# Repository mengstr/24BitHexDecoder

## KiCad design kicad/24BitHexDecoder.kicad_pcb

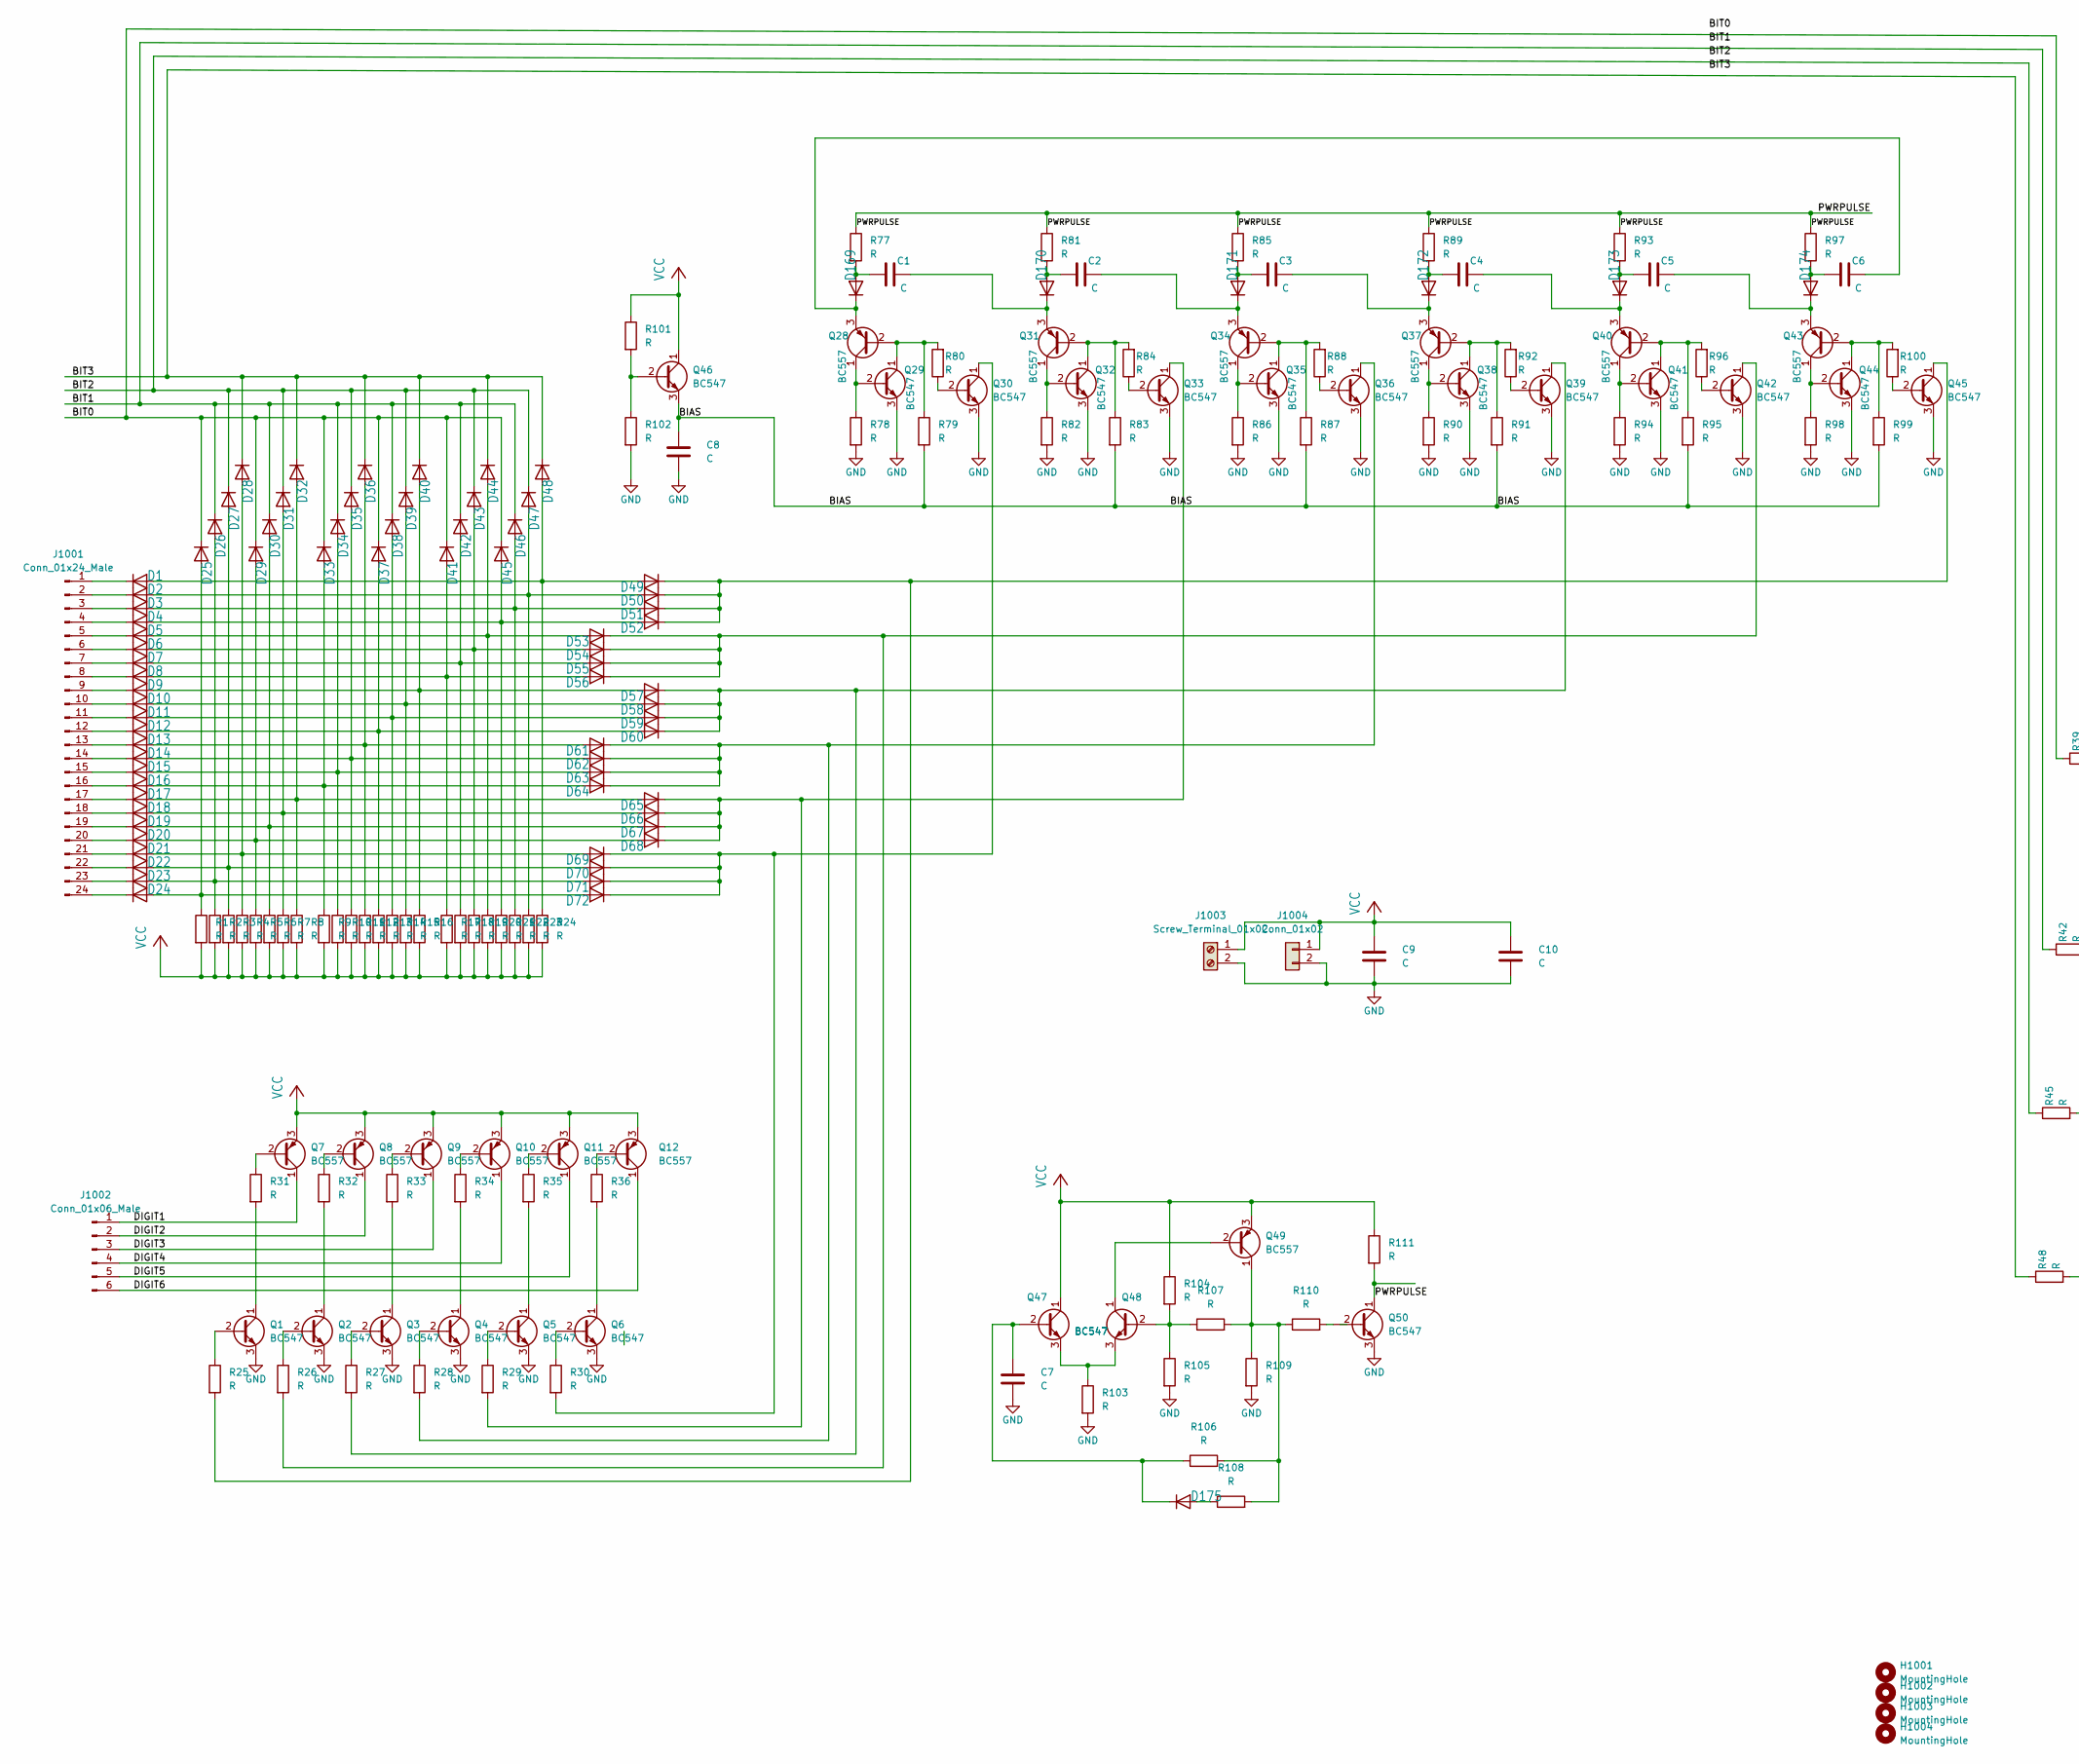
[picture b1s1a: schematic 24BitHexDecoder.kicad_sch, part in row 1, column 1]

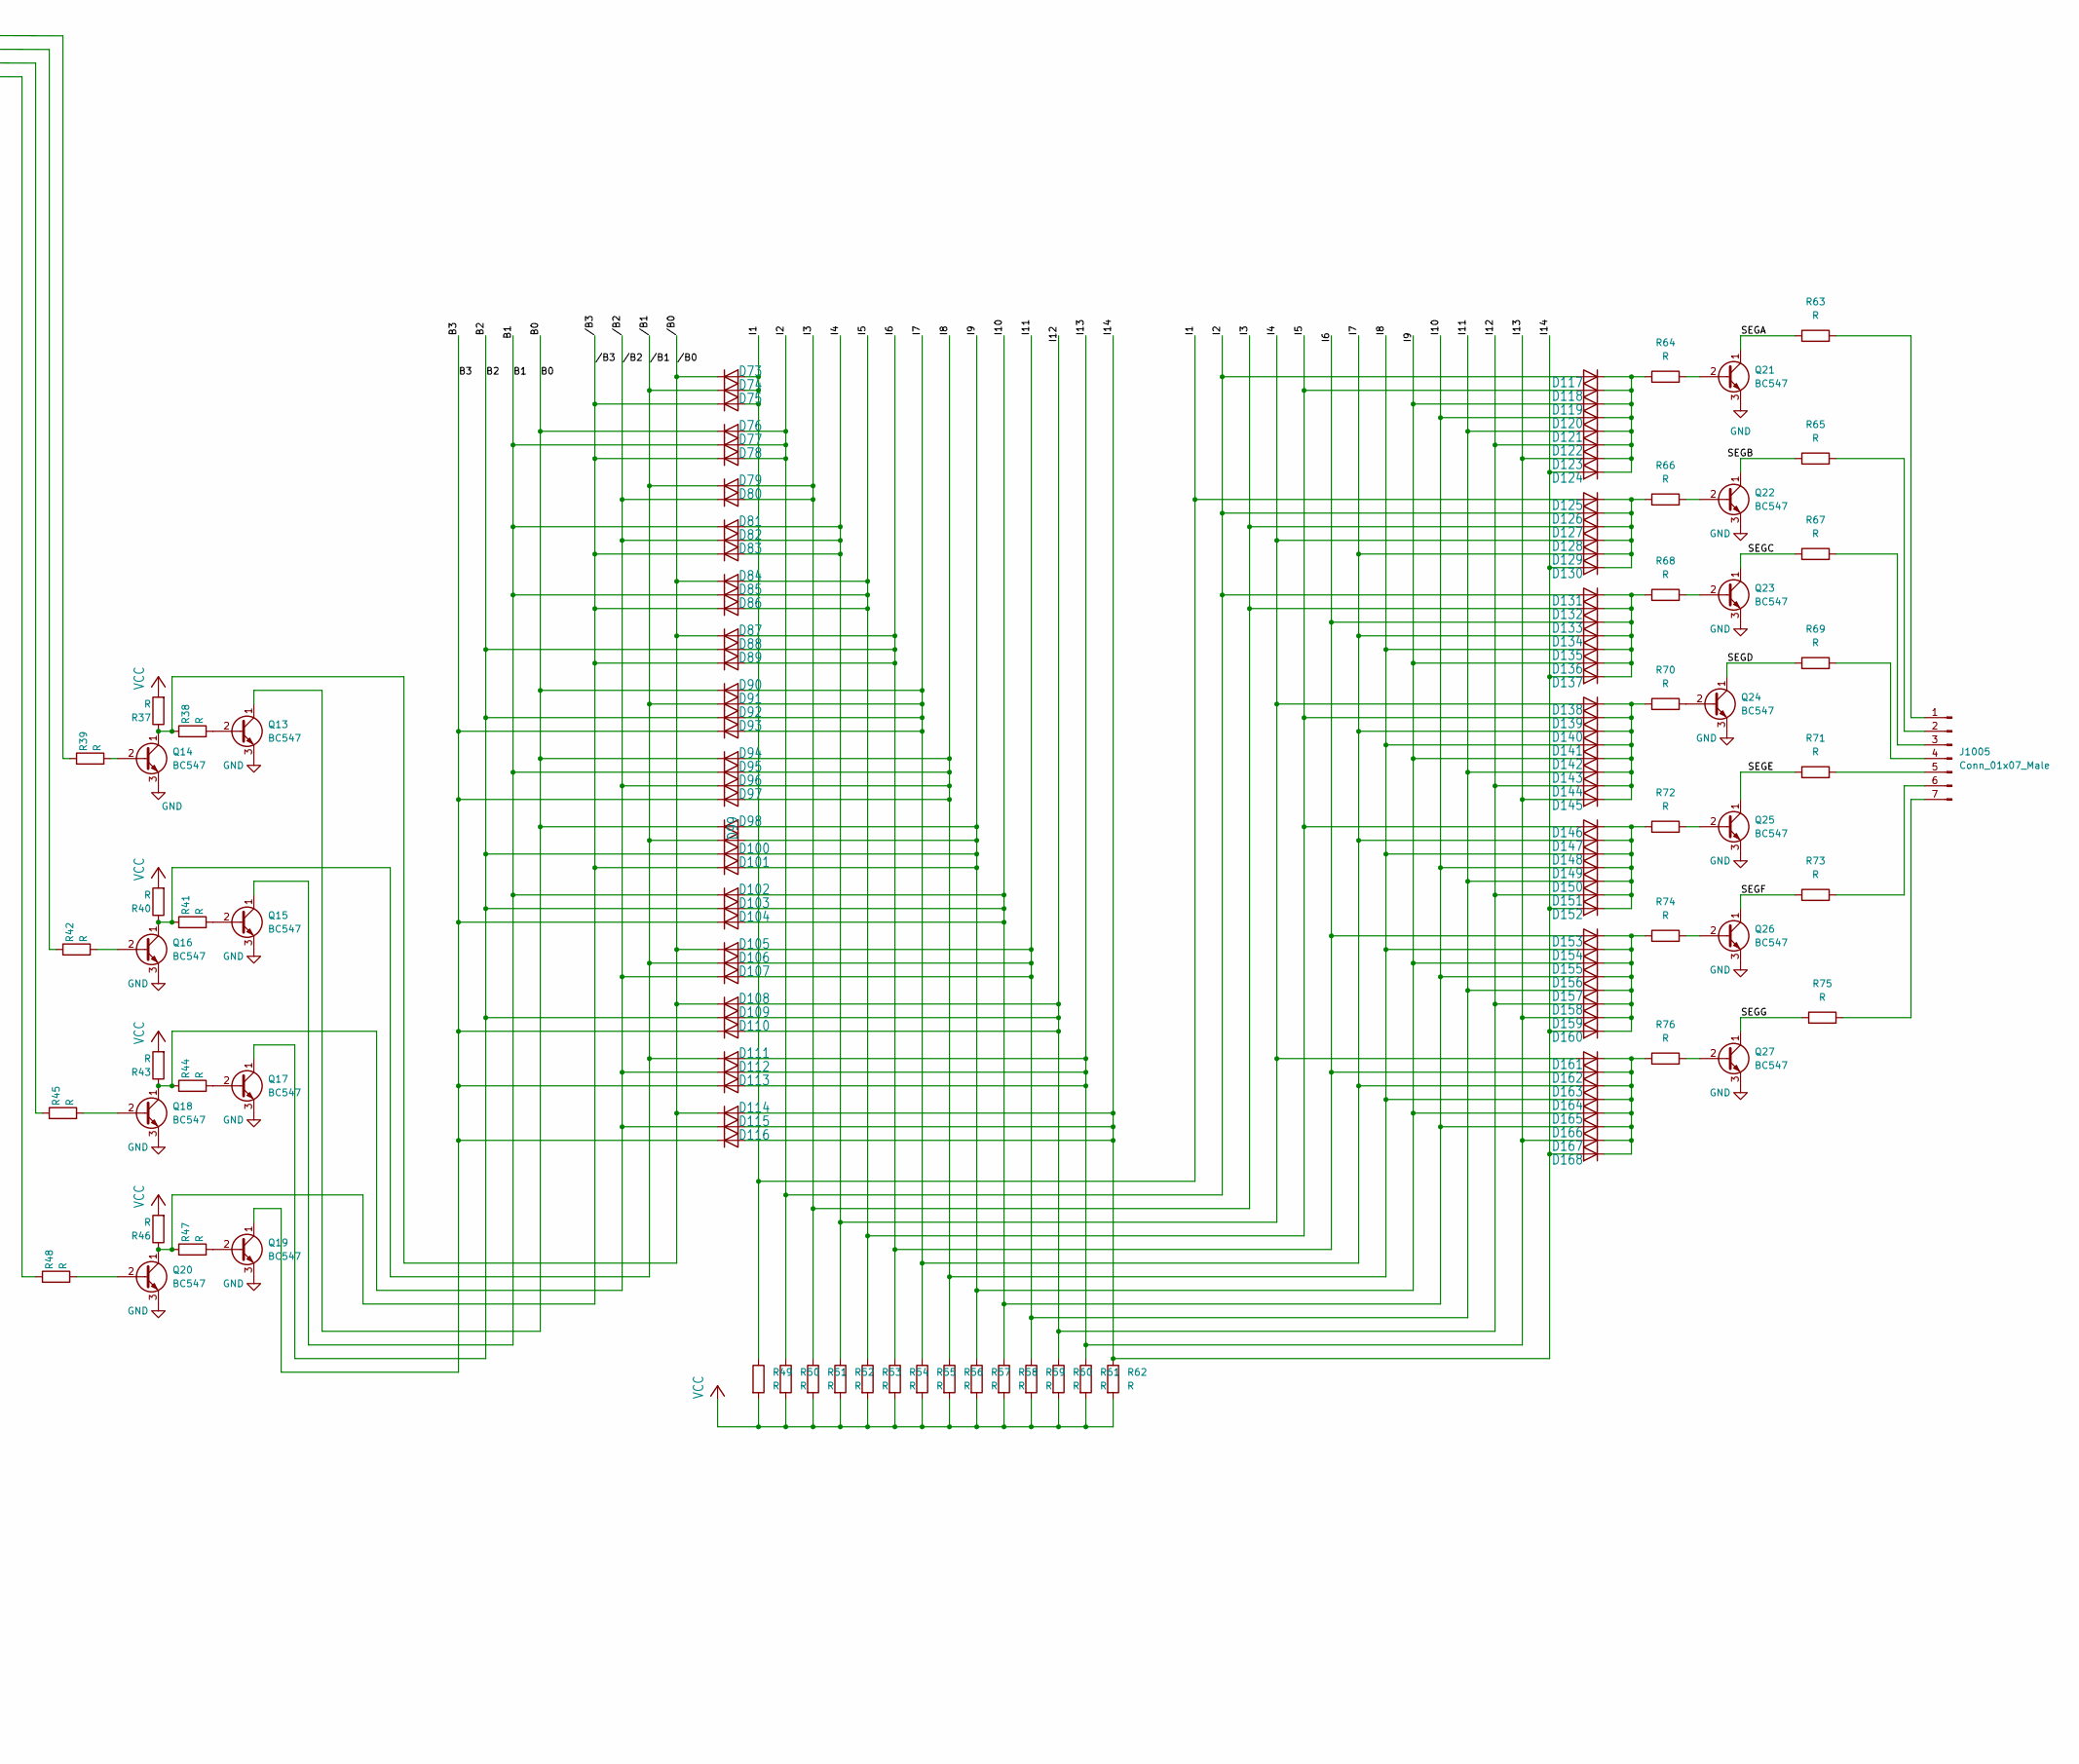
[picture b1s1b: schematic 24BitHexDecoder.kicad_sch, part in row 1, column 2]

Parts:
C1, C2, C3, C4, C5, C6, C7: C; C_Disc_D9.0mm_W2.5mm_P5.00mm
C8, C9, C10: C; CP_Radial_D5.0mm_P2.50mm
D1, D2, D3, D4, D5, D6, D7, D8, D9, D10, D11, D12, D13, D14, D15, D16, D17, D18, D19, D20, D21, D22, D23, D24, D25, D26, D27, D28, D29, D30, D31, D32, D33, D34, D35, D36, D37, D38, D39, D40, D41, D42, D43, D44, D45, D46, D47, D48, D49, D50, D51, D52, D53, D54, D55, D56, D57, D58, D59, D60, D61, D62, D63, D64, D65, D66, D67, D68, D69, D70, D71, D72, D73, D74, D75, D76, D77, D78, D79, D80, D81, D82, D83, D84, D85, D86, D87, D88, D89, D90, D91, D92, D93, D94, D95, D96, D97, D98, D99, D100, D101, D102, D103, D104, D105, D106, D107, D108, D109, D110, D111, D112, D113, D114, D115, D116, D117, D118, D119, D120, D121, D122, D123, D124, D125, D126, D127, D128, D129, D130, D131, D132, D133, D134, D135, D136, D137, D138, D139, D140, D141, D142, D143, D144, D145, D146, D147, D148, D149, D150, D151, D152, D153, D154, D155, D156, D157, D158, D159, D160, D161, D162, D163, D164, D165, D166, D167, D168, D169, D170, D171, D172, D173, D174, D175: SMALL_DIODEDO35-7; D_DO-35_P7.62_SmallPads
H1001, H1002, H1003, H1004: MountingHole; MountingHole_3.2mm_M3
J1001: Conn_01x24_Male; PinHeader_1x24_P2.54mm_Vertical
J1002: Conn_01x06_Male; PinHeader_1x06_P2.54mm_Vertical
J1003: Screw_Terminal_01x02; TerminalBlock_TE_282834-2_1x02_P2.54mm_Horizontal
J1004: Conn_01x02; PinHeader_1x02_P2.54mm_Vertical
J1005: Conn_01x07_Male; PinHeader_1x07_P2.54mm_Vertical
Q1, Q2, Q3, Q4, Q5, Q6, Q13, Q14, Q15, Q16, Q17, Q18, Q19, Q20, Q21, Q22, Q23, Q24, Q25, Q26, Q27, Q29, Q30, Q32, Q33, Q35, Q36, Q38, Q39, Q41, Q42, Q44, Q45, Q46, Q47, Q48, Q50: BC547; TO-92_NPN_Spaced
Q7, Q8, Q9, Q10, Q11, Q12, Q28, Q31, Q34, Q37, Q40, Q43, Q49: BC557; TO-92_PNP_Spaced
R1, R2, R3, R4, R5, R6, R7, R8, R9, R10, R11, R12, R13, R14, R15, R16, R17, R18, R19, R20, R21, R22, R23, R24, R25, R26, R27, R28, R29, R30, R31, R32, R33, R34, R35, R36, R37, R38, R39, R40, R41, R42, R43, R44, R45, R46, R47, R48, R49, R50, R51, R52, R53, R54, R55, R56, R57, R58, R59, R60, R61, R62, R63, R64, R65, R66, R67, R68, R69, R70, R71, R72, R73, R74, R75, R76, R77, R78, R79, R80, R81, R82, R83, R84, R85, R86, R87, R88, R89, R90, R91, R92, R93, R94, R95, R96, R97, R98, R99, R100, R101, R102, R103, R104, R105, R106, R107, R108, R109, R110, R111: R; R_L3.6mm_D1.6mm_P7.62mm_NoTop

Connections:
/B0: D76.1 (K), D90.1 (K), D94.1 (K), D98.1 (K), Q13.1 (C)
/B1: D77.1 (K), D81.1 (K), D85.1 (K), D95.1 (K), D102.1 (K), Q15.1 (C)
/B2: D88.1 (K), D92.1 (K), D100.1 (K), D103.1 (K), D109.1 (K), Q17.1 (C)
/B3: D93.1 (K), D97.1 (K), D104.1 (K), D110.1 (K), D113.1 (K), D116.1 (K), Q19.1 (C)
/BIAS: C8.1, Q46.3 (E), R79.2, R83.2, R87.2, R91.2, R95.2, R99.2
/BIT0: D25.1 (K), D29.1 (K), D33.1 (K), D37.1 (K), D41.1 (K), D45.1 (K), R39.1
/BIT1: D26.1 (K), D30.1 (K), D34.1 (K), D38.1 (K), D42.1 (K), D46.1 (K), R42.1
/BIT2: D27.1 (K), D31.1 (K), D35.1 (K), D39.1 (K), D43.1 (K), D47.1 (K), R45.1
/BIT3: D28.1 (K), D32.1 (K), D36.1 (K), D40.1 (K), D44.1 (K), D48.1 (K), R48.1
/DIGIT1: J1002.1, Q7.1 (C)
/DIGIT2: J1002.2, Q8.1 (C)
/DIGIT3: J1002.3, Q9.1 (C)
/DIGIT4: J1002.4, Q10.1 (C)
/DIGIT5: J1002.5, Q11.1 (C)
/DIGIT6: J1002.6, Q12.1 (C)
/I1: D73.2 (A), D74.2 (A), D75.2 (A), D125.2 (A), R49.1
/I2: D76.2 (A), D77.2 (A), D78.2 (A), D117.2 (A), D126.2 (A), D131.2 (A), R50.1
/I3: D79.2 (A), D80.2 (A), D127.2 (A), D132.2 (A), R51.1
/I4: D81.2 (A), D82.2 (A), D83.2 (A), D128.2 (A), D138.2 (A), D161.2 (A), R52.1
/I5: D84.2 (A), D85.2 (A), D86.2 (A), D118.2 (A), D139.2 (A), D146.2 (A), R53.1
/I6: D87.2 (A), D88.2 (A), D89.2 (A), D133.2 (A), D153.2 (A), D162.2 (A), R54.1
/I7: D90.2 (A), D91.2 (A), D92.2 (A), D93.2 (A), D129.2 (A), D134.2 (A), D140.2 (A), D147.2 (A), D163.2 (A), R55.1
/I8: D94.2 (A), D95.2 (A), D96.2 (A), D97.2 (A), D135.2 (A), D141.2 (A), D148.2 (A), D154.2 (A), D164.2 (A), R56.1
/I9: D98.2 (A), D99.2 (A), D100.2 (A), D101.2 (A), D119.2 (A), D136.2 (A), D142.2 (A), D155.2 (A), D165.2 (A), R57.1
/I10: D102.2 (A), D103.2 (A), D104.2 (A), D120.2 (A), D149.2 (A), D156.2 (A), D166.2 (A), R58.1
/I11: D105.2 (A), D106.2 (A), D107.2 (A), D121.2 (A), D143.2 (A), D150.2 (A), D157.2 (A), R59.1
/I12: D108.2 (A), D109.2 (A), D110.2 (A), D122.2 (A), D144.2 (A), D151.2 (A), D158.2 (A), R60.1
/I13: D111.2 (A), D112.2 (A), D113.2 (A), D123.2 (A), D145.2 (A), D159.2 (A), D167.2 (A), R61.1
/I14: D114.2 (A), D115.2 (A), D116.2 (A), D124.2 (A), D130.2 (A), D137.2 (A), D152.2 (A), D160.2 (A), D168.2 (A), R62.1
/PWRPULSE: Q50.1 (C), R77.1, R81.1, R85.1, R89.1, R93.1, R97.1, R111.2
/SEGA: Q21.1 (C), R63.1
/SEGC: Q23.1 (C), R67.1
/SEGD: Q24.1 (C), R69.1
/SEGE: Q25.1 (C), R71.1
/SEGF: Q26.1 (C), R73.1
/SEGG: Q27.1 (C), R75.1
//B0: D73.1 (K), D84.1 (K), D87.1 (K), D105.1 (K), D108.1 (K), D114.1 (K), Q14.1 (C), R37.1, R38.1
//B1: D74.1 (K), D79.1 (K), D91.1 (K), D99.1 (K), D106.1 (K), D111.1 (K), Q16.1 (C), R40.1, R41.1
//B2: D80.1 (K), D82.1 (K), D96.1 (K), D107.1 (K), D112.1 (K), D115.1 (K), Q18.1 (C), R43.1, R44.1
//B3: D75.1 (K), D78.1 (K), D83.1 (K), D86.1 (K), D89.1 (K), D101.1 (K), Q20.1 (C), R46.1, R47.1
GND: C7.2, C8.2, C9.2, C10.2, J1003.2, J1004.2, Q1.3 (E), Q2.3 (E), Q3.3 (E), Q4.3 (E), Q5.3 (E), Q6.3 (E), Q13.3 (E), Q14.3 (E), Q15.3 (E), Q16.3 (E), Q17.3 (E), Q18.3 (E), Q19.3 (E), Q20.3 (E), Q21.3 (E), Q22.3 (E), Q23.3 (E), Q24.3 (E), Q25.3 (E), Q26.3 (E), Q27.3 (E), Q29.3 (E), Q30.3 (E), Q32.3 (E), Q33.3 (E), Q35.3 (E), Q36.3 (E), Q38.3 (E), Q39.3 (E), Q41.3 (E), Q42.3 (E), Q44.3 (E), Q45.3 (E), Q50.3 (E), R78.2, R82.2, R86.2, R90.2, R94.2, R98.2, R102.2, R103.2, R105.2, R109.2
unnamed: C1.1, D170.1 (K), Q31.3 (E)
unnamed: C1.2, D169.2 (A), R77.2
unnamed: C2.1, D171.1 (K), Q34.3 (E)
unnamed: C2.2, D170.2 (A), R81.2
unnamed: C3.1, D172.1 (K), Q37.3 (E)
unnamed: C3.2, D171.2 (A), R85.2
unnamed: C4.1, D173.1 (K), Q40.3 (E)
unnamed: C4.2, D172.2 (A), R89.2
unnamed: C5.1, D174.1 (K), Q43.3 (E)
unnamed: C5.2, D173.2 (A), R93.2
unnamed: C6.1, D169.1 (K), Q28.3 (E)
unnamed: C6.2, D174.2 (A), R97.2
unnamed: C7.1, D175.1 (K), Q47.2 (B), R106.1
unnamed: D1.2 (A), D48.2 (A), D49.2 (A), R24.1
unnamed: D2.2 (A), D47.2 (A), D50.2 (A), R23.1
unnamed: D3.2 (A), D46.2 (A), D51.2 (A), R22.1
unnamed: D4.2 (A), D45.2 (A), D52.2 (A), R21.1
unnamed: D5.1 (K), J1001.5
unnamed: D9.1 (K), J1001.9
unnamed: D10.2 (A), D39.2 (A), D58.2 (A), R15.1
unnamed: D11.2 (A), D38.2 (A), D59.2 (A), R14.1
unnamed: D12.2 (A), D37.2 (A), D60.2 (A), R13.1
unnamed: D13.2 (A), D36.2 (A), D61.2 (A), R12.1
unnamed: D14.2 (A), D35.2 (A), D62.2 (A), R11.1
unnamed: D15.2 (A), D34.2 (A), D63.2 (A), R10.1
unnamed: D16.2 (A), D33.2 (A), D64.2 (A), R9.1
unnamed: D17.2 (A), D32.2 (A), D65.2 (A), R8.1
unnamed: D18.2 (A), D31.2 (A), D66.2 (A), R7.1
unnamed: D19.2 (A), D30.2 (A), D67.2 (A), R6.1
unnamed: D20.1 (K), J1001.20
unnamed: D20.2 (A), D29.2 (A), D68.2 (A), R5.1
unnamed: D21.2 (A), D28.2 (A), D69.2 (A), R4.1
unnamed: D22.2 (A), D27.2 (A), D70.2 (A), R3.1
unnamed: D23.1 (K), J1001.23
unnamed: D23.2 (A), D26.2 (A), D71.2 (A), R2.1
unnamed: D24.1 (K), J1001.24
unnamed: D24.2 (A), D25.2 (A), D72.2 (A), R1.1
unnamed: D9.2 (A), D40.2 (A), D57.2 (A), R16.1
unnamed: D8.2 (A), D41.2 (A), D56.2 (A), R17.1
unnamed: D7.2 (A), D42.2 (A), D55.2 (A), R18.1
unnamed: D6.2 (A), D43.2 (A), D54.2 (A), R19.1
unnamed: D5.2 (A), D44.2 (A), D53.2 (A), R20.1
unnamed: D49.1 (K), D50.1 (K), D51.1 (K), D52.1 (K), Q45.1 (C), R25.2
unnamed: D53.1 (K), D54.1 (K), D55.1 (K), D56.1 (K), Q42.1 (C), R26.2
unnamed: D57.1 (K), D58.1 (K), D59.1 (K), D60.1 (K), Q39.1 (C), R27.2
unnamed: D61.1 (K), D62.1 (K), D63.1 (K), D64.1 (K), Q36.1 (C), R28.2
unnamed: D65.1 (K), D66.1 (K), D67.1 (K), D68.1 (K), Q33.1 (C), R29.2
unnamed: D69.1 (K), D70.1 (K), D71.1 (K), D72.1 (K), Q30.1 (C), R30.2
unnamed: D117.1 (K), D118.1 (K), D119.1 (K), D120.1 (K), D121.1 (K), D122.1 (K), D123.1 (K), D124.1 (K), R64.1
unnamed: D125.1 (K), D126.1 (K), D127.1 (K), D128.1 (K), D129.1 (K), D130.1 (K), R66.1
unnamed: D131.1 (K), D132.1 (K), D133.1 (K), D134.1 (K), D135.1 (K), D136.1 (K), D137.1 (K), R68.1
unnamed: D138.1 (K), D139.1 (K), D140.1 (K), D141.1 (K), D142.1 (K), D143.1 (K), D144.1 (K), D145.1 (K), R70.1
unnamed: D146.1 (K), D147.1 (K), D148.1 (K), D149.1 (K), D150.1 (K), D151.1 (K), D152.1 (K), R72.1
unnamed: D153.1 (K), D154.1 (K), D155.1 (K), D156.1 (K), D157.1 (K), D158.1 (K), D159.1 (K), D160.1 (K), R74.1
unnamed: D161.1 (K), D162.1 (K), D163.1 (K), D164.1 (K), D165.1 (K), D166.1 (K), D167.1 (K), D168.1 (K), R76.1
unnamed: D175.2 (A), R108.1
unnamed: D1.1 (K), J1001.1
unnamed: D2.1 (K), J1001.2
unnamed: D3.1 (K), J1001.3
unnamed: D4.1 (K), J1001.4
unnamed: D6.1 (K), J1001.6
unnamed: D7.1 (K), J1001.7
unnamed: D8.1 (K), J1001.8
unnamed: D10.1 (K), J1001.10
unnamed: D11.1 (K), J1001.11
unnamed: D12.1 (K), J1001.12
unnamed: D13.1 (K), J1001.13
unnamed: D14.1 (K), J1001.14
unnamed: D15.1 (K), J1001.15
unnamed: D16.1 (K), J1001.16
unnamed: D17.1 (K), J1001.17
unnamed: D18.1 (K), J1001.18
unnamed: D19.1 (K), J1001.19
unnamed: D21.1 (K), J1001.21
unnamed: D22.1 (K), J1001.22
unnamed: J1005.1, R63.2
unnamed: J1005.2, R65.2
unnamed: J1005.3, R67.2
unnamed: J1005.4, R69.2
unnamed: J1005.5, R71.2
unnamed: J1005.6, R73.2
unnamed: J1005.7, R75.2
unnamed: Q1.1 (C), R31.2
unnamed: Q1.2 (B), R25.1
unnamed: Q2.1 (C), R32.2
unnamed: Q2.2 (B), R26.1
unnamed: Q3.1 (C), R33.2
unnamed: Q3.2 (B), R27.1
unnamed: Q4.1 (C), R34.2
unnamed: Q4.2 (B), R28.1
unnamed: Q5.1 (C), R35.2
unnamed: Q5.2 (B), R29.1
unnamed: Q6.1 (C), R36.2
unnamed: Q6.2 (B), R30.1
unnamed: Q7.2 (B), R31.1
unnamed: Q8.2 (B), R32.1
unnamed: Q9.2 (B), R33.1
unnamed: Q10.2 (B), R34.1
unnamed: Q11.2 (B), R35.1
unnamed: Q12.2 (B), R36.1
unnamed: Q13.2 (B), R38.2
unnamed: Q14.2 (B), R39.2
unnamed: Q15.2 (B), R41.2
unnamed: Q16.2 (B), R42.2
unnamed: Q17.2 (B), R44.2
unnamed: Q18.2 (B), R45.2
unnamed: Q19.2 (B), R47.2
unnamed: Q20.2 (B), R48.2
unnamed: Q21.2 (B), R64.2
unnamed: Q22.1 (C), R65.1
unnamed: Q22.2 (B), R66.2
unnamed: Q23.2 (B), R68.2
unnamed: Q24.2 (B), R70.2
unnamed: Q25.2 (B), R72.2
unnamed: Q26.2 (B), R74.2
unnamed: Q27.2 (B), R76.2
unnamed: Q28.1 (C), Q29.2 (B), R78.1
unnamed: Q28.2 (B), Q29.1 (C), R79.1, R80.2
unnamed: Q30.2 (B), R80.1
unnamed: Q31.1 (C), Q32.2 (B), R82.1
unnamed: Q31.2 (B), Q32.1 (C), R83.1, R84.2
unnamed: Q33.2 (B), R84.1
unnamed: Q34.1 (C), Q35.2 (B), R86.1
unnamed: Q34.2 (B), Q35.1 (C), R87.1, R88.2
unnamed: Q36.2 (B), R88.1
unnamed: Q37.1 (C), Q38.2 (B), R90.1
unnamed: Q37.2 (B), Q38.1 (C), R91.1, R92.2
unnamed: Q39.2 (B), R92.1
unnamed: Q40.1 (C), Q41.2 (B), R94.1
unnamed: Q40.2 (B), Q41.1 (C), R95.1, R96.2
unnamed: Q42.2 (B), R96.1
unnamed: Q43.1 (C), Q44.2 (B), R98.1
unnamed: Q43.2 (B), Q44.1 (C), R99.1, R100.2
unnamed: Q45.2 (B), R100.1
unnamed: Q46.2 (B), R101.2, R102.1
unnamed: Q47.3 (E), Q48.3 (E), R103.1
unnamed: Q48.1 (C), Q49.2 (B)
unnamed: Q48.2 (B), R104.2, R105.1, R107.1
unnamed: Q49.1 (C), R106.2, R107.2, R108.2, R109.1, R110.1
unnamed: Q50.2 (B), R110.2
VCC: C9.1, C10.1, J1003.1, J1004.1, Q7.3 (E), Q8.3 (E), Q9.3 (E), Q10.3 (E), Q11.3 (E), Q12.3 (E), Q46.1 (C), Q47.1 (C), Q49.3 (E), R1.2, R2.2, R3.2, R4.2, R5.2, R6.2, R7.2, R8.2, R9.2, R10.2, R11.2, R12.2, R13.2, R14.2, R15.2, R16.2, R17.2, R18.2, R19.2, R20.2, R21.2, R22.2, R23.2, R24.2, R37.2, R40.2, R43.2, R46.2, R49.2, R50.2, R51.2, R52.2, R53.2, R54.2, R55.2, R56.2, R57.2, R58.2, R59.2, R60.2, R61.2, R62.2, R101.1, R104.1, R111.1

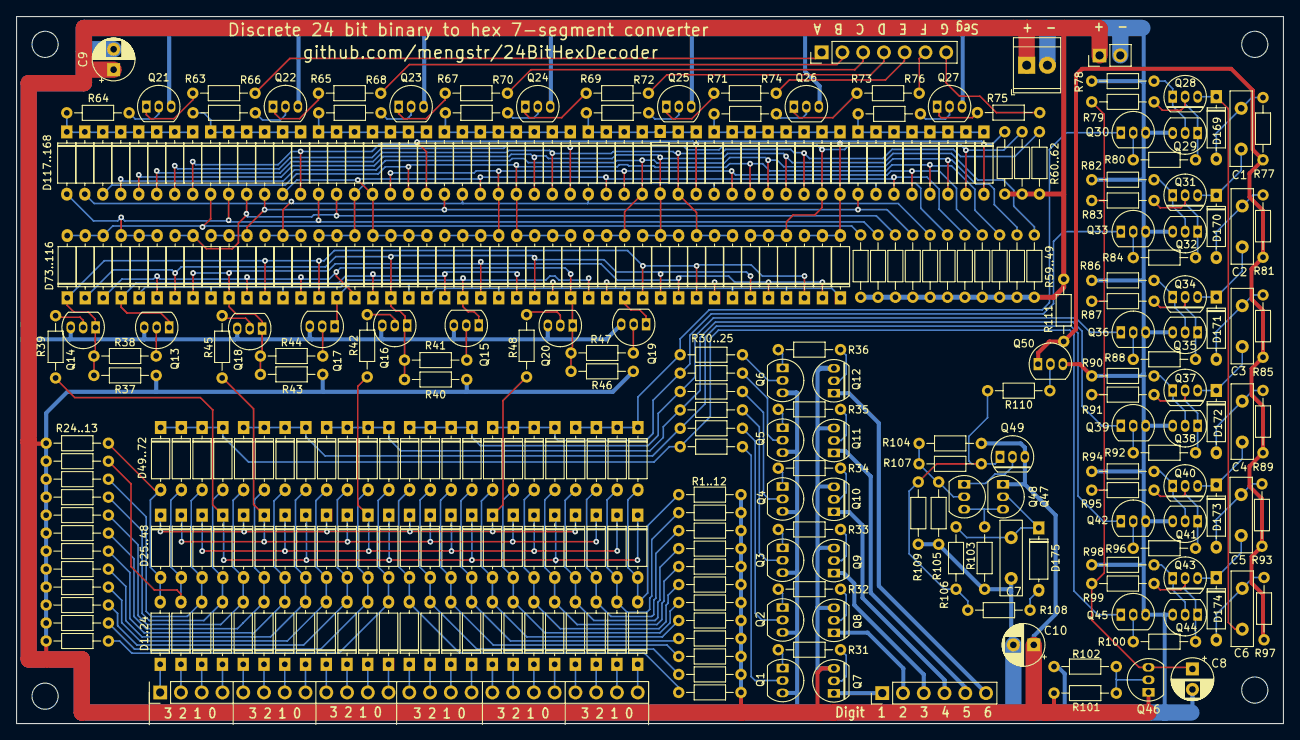
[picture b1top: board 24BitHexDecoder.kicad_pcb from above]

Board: 2 copper layers, 155.0 x 86.5 mm, 355 parts (0 on the bottom side), 182 nets.

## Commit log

2022-08-09 Add frame to schematic
2022-08-09 Add LTspice simulation
